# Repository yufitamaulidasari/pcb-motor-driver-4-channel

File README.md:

# pcb-motor-driver-4-channel
Desain PCB 4-channel motor driver L298N, ESP32, MPU6050 menggunakan KiCad.

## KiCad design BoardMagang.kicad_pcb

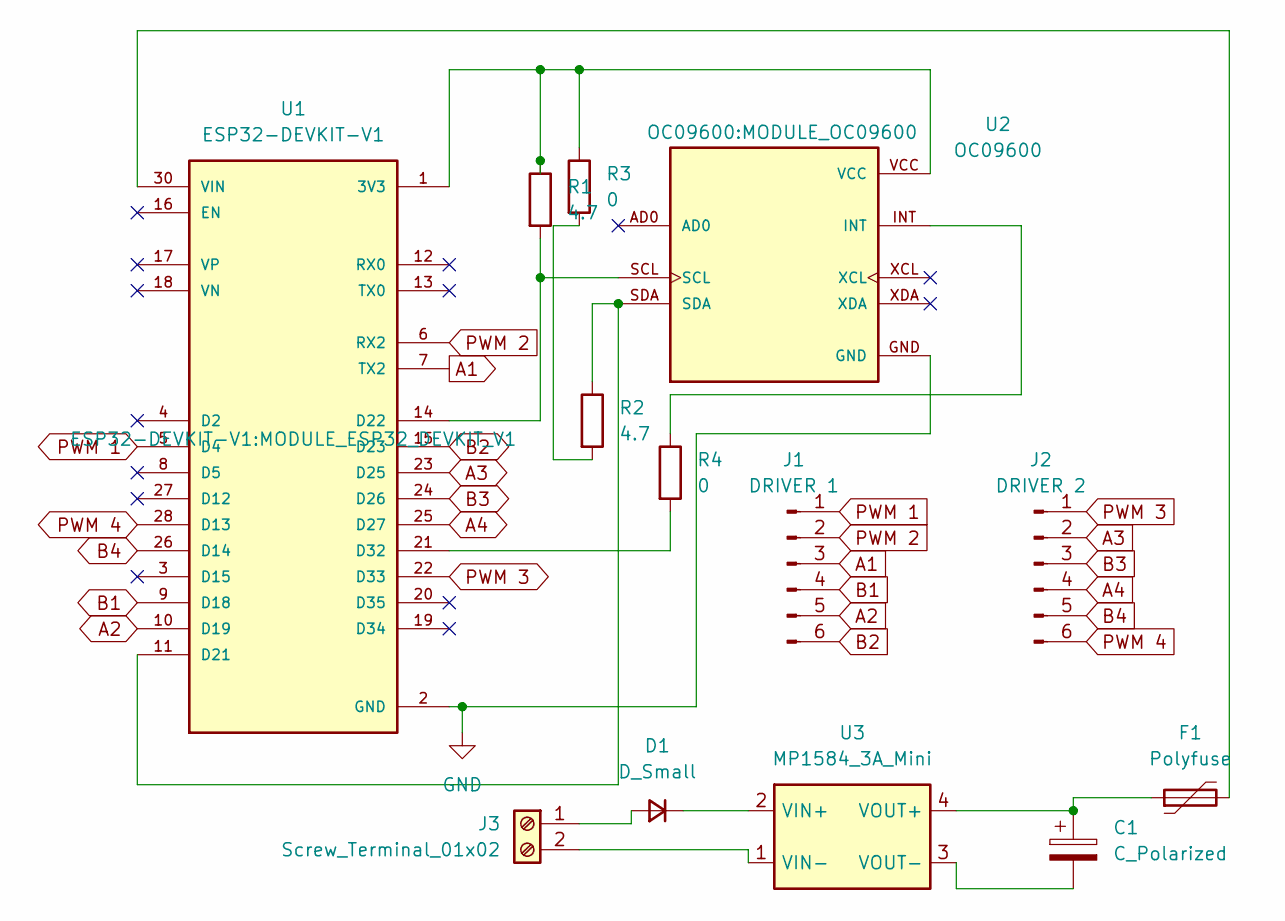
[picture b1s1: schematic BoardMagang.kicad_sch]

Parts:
C1: C_Polarized; C_Radial_D6.3mm_H11.0mm_P2.50mm
D1: D_Small; D_SMA
F1: Polyfuse; Fuse_1812_4532Metric
J1: DRIVER 1; PinHeader_1x06_P2.54mm_Vertical
J2: DRIVER 2; PinHeader_1x06_P2.54mm_Vertical
J3: Screw_Terminal_01x02; TerminalBlock_MaiXu_MX126-5.0-02P_1x02_P5.00mm
R1, R2: 4.7; R_Axial_DIN0204_L3.6mm_D1.6mm_P5.08mm_Horizontal
R3, R4: 0; R_Axial_DIN0204_L3.6mm_D1.6mm_P5.08mm_Horizontal
U1: ESP32-DEVKIT-V1; MODULE_ESP32_DEVKIT_V1; PARTREV N/A
U2: OC09600; MODULE_OC09600; PARTREV NA
U3: MP1584_3A_Mini; MP1584_Module

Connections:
A1: J1.3, U1.7 (TX2)
A2: J1.5, U1.10 (D19)
A3: J2.2, U1.23 (D25)
A4: J2.4, U1.25 (D27)
B1: J1.4, U1.9 (D18)
B2: J1.6, U1.15 (D23)
B3: J2.3, U1.24 (D26)
B4: J2.5, U1.26 (D14)
GND: U1.2 (GND), U1.29 (GND), U2.GND
unnamed: D1.2 (A), J3.1
unnamed: D1.1 (K), U3.2 (VIN+)
unnamed: J3.2, U3.1 (VIN-)
unnamed: R2.2, R3.2
unnamed: R4.1, U2.INT
unnamed: R1.1, R3.1, U1.1 (3V3), U2.VCC
unnamed: R2.1, U1.11 (D21), U2.SDA
unnamed: R1.2, U1.14 (D22), U2.SCL
unnamed: R4.2, U1.21 (D32)
unnamed: F1.2, U1.30 (VIN)
unnamed: C1.1, F1.1, U3.4 (VOUT+)
unnamed: C1.2, U3.3 (VOUT-)
PWM 1: J1.1, U1.5 (D4)
PWM 2: J1.2, U1.6 (RX2)
PWM 3: J2.1, U1.22 (D33)
PWM 4: J2.6, U1.28 (D13)

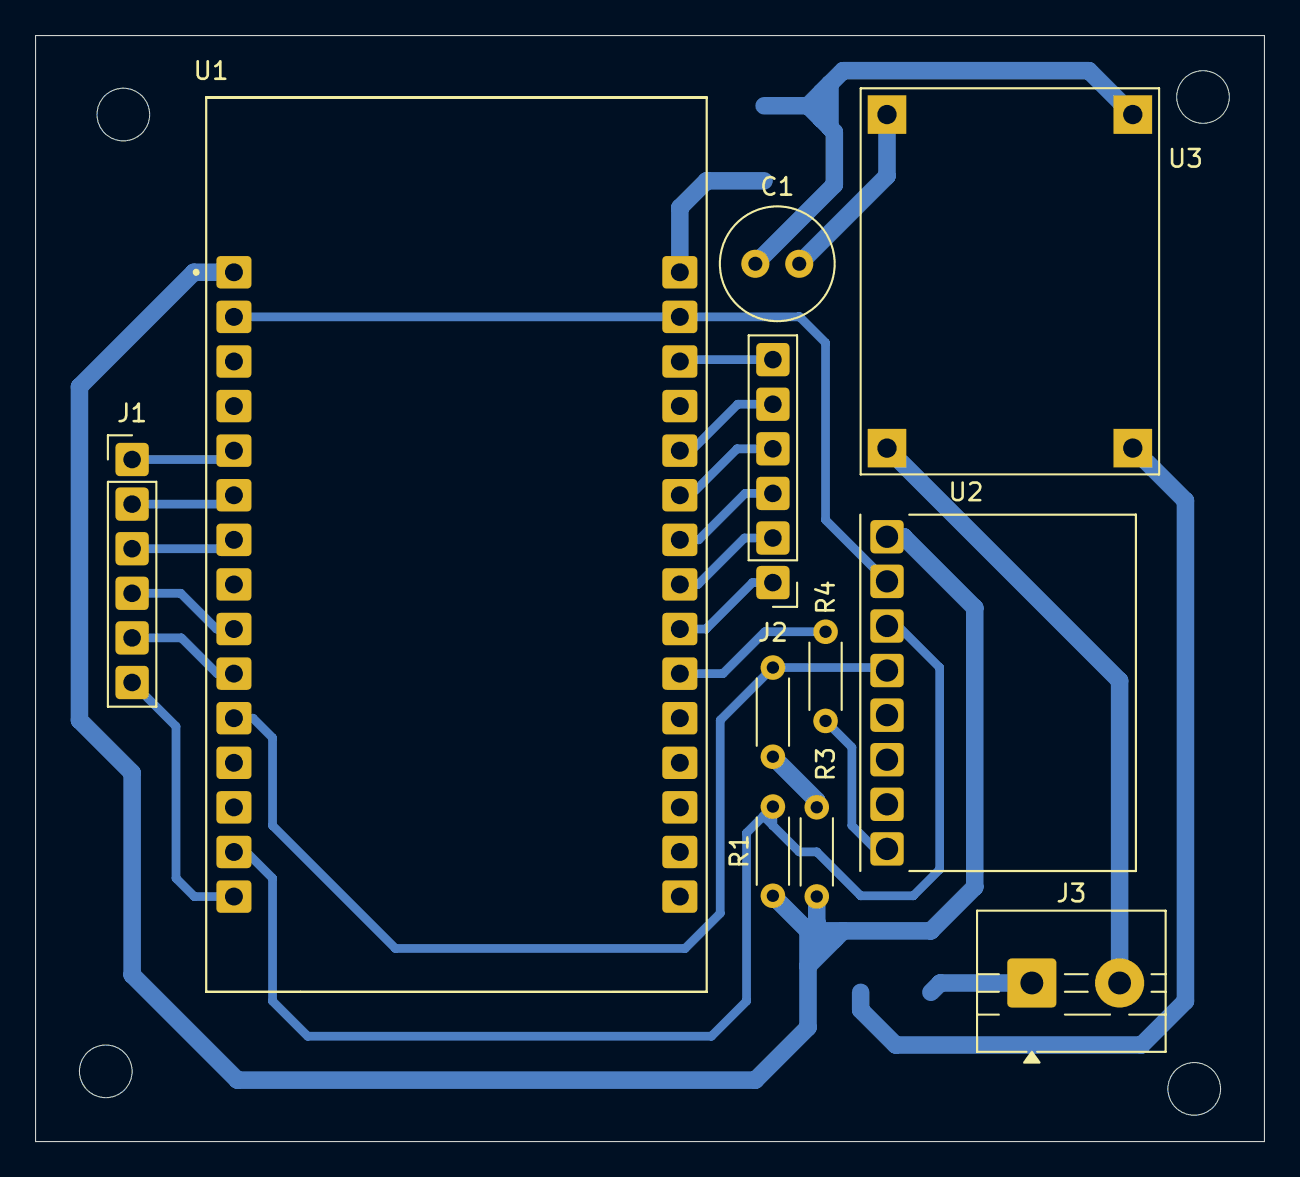
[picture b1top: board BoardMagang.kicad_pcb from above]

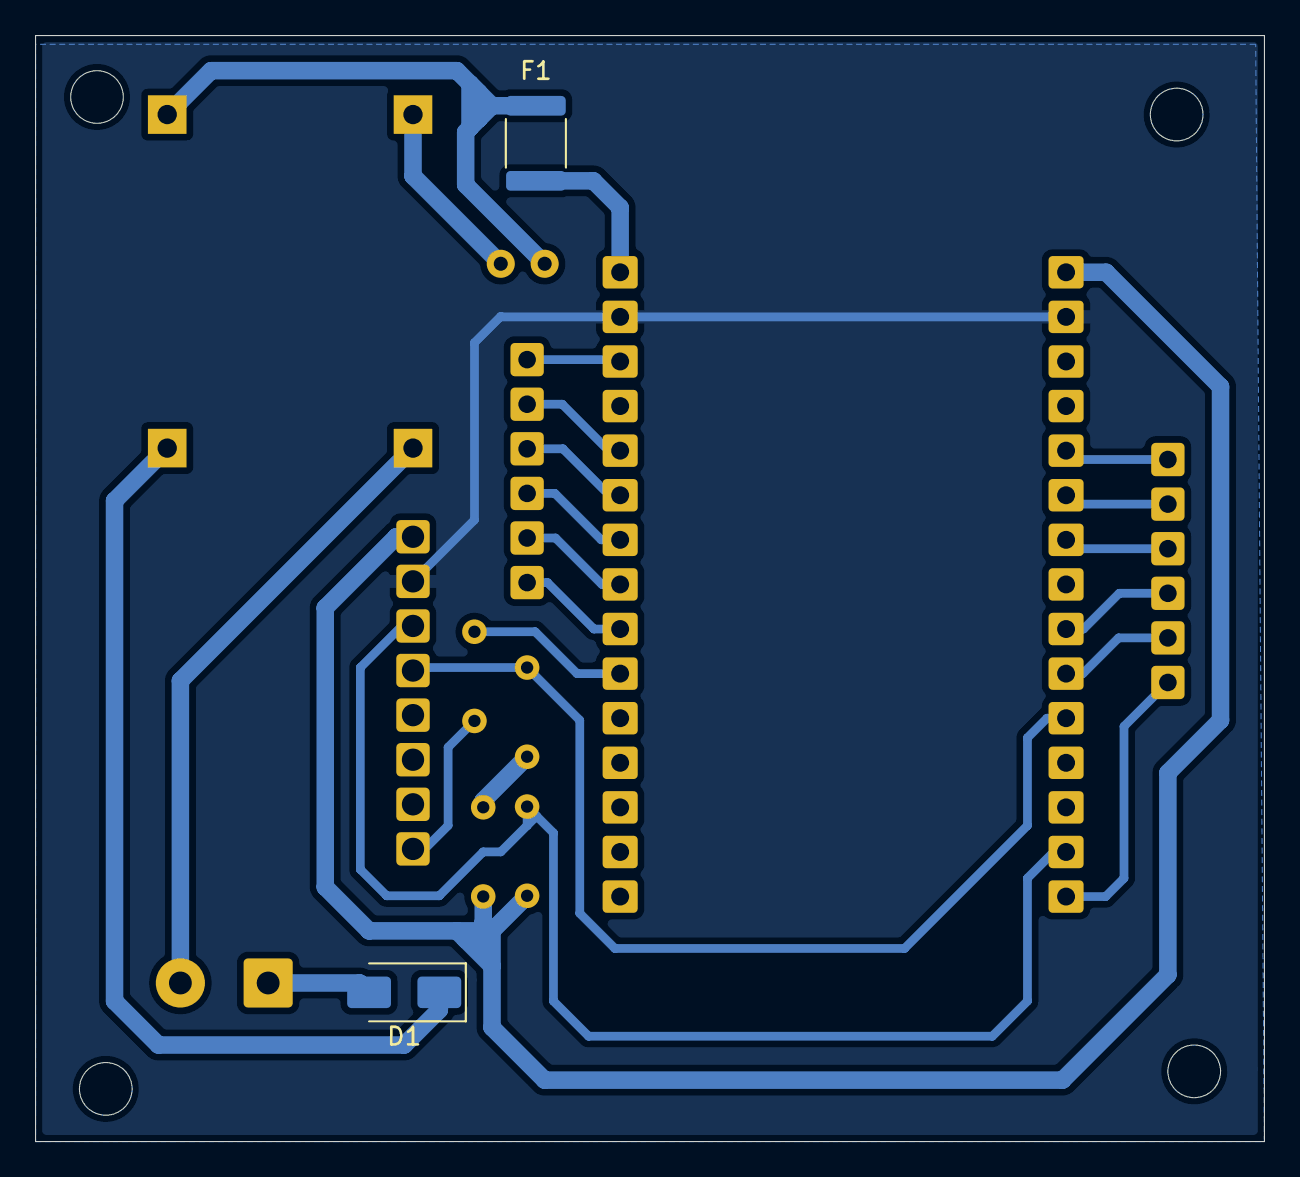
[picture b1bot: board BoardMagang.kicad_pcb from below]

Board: 2 copper layers, 70.0 x 63.0 mm, 13 parts (2 on the bottom side), 25 nets.
